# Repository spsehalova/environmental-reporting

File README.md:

# environmental-reporting

**WORK IN PROGRESS**

Enviromentalne merania

## Mesured parameters

| Parameter					| Unit			| Description							| Module									| Range			|
|---------------------------|---------------|---------------------------------------|-------------------------------------------|---------------|
| Temperature				| °C			| Ambient temperature					| BME680 									|				|
| Humidity					| %				| Relative humidity						| BME680 									|				|
| Pressure					| hPa			| Atmospheric pressure					| BME680 									|				|
| IAQ						| adaptive IAQ	| Indoor air quality index				| BME680 									| 0 - 500   	|
| sIAQ						| unscaled IAQ	| static indoor air quality index		| BME680 									| 0 - 10171		|
| eCO₂						| ppm			| Equivalent CO₂ concentration			| BME680 									| 0.5 - 1000	|
| CO₂						| ppm			| CO₂ concentration						| SEN63C 									| 				|
| bVOC						| ppm			| breath volatile organic compounds		| BME680 									| 400 - ...		|
| Compensated Gas Resistace	| Ohm			| Compensated gas resistance			| BME680 									|				|
| Gas Percentage			| %				| Gas percentage						| BME680 									|				|
| Light						| lux			| Ambient light intensity				| BH1750									|				|
| Noise						| rel dB		| Ambient noise level					| INMP441									|				|
| PM2.5/1.0/4.0/10.0		| mg/m³			| Particulate matter x concentration	| SEN63C									|				|
| Nearby Device Count		| count			| Number of nearby BLE devices			| ESP32										|				|
| Dew Point					| °C			| Dew point temperature					| Calculated from Temperature and Humidity	|				| 
| Absolute Humidity			| g/m³			| Absolute humidity						| Calculated from Temperature and Humidity	|				|
| Mold Risk 				| VTT Index		| Mold risk index						| Calculated from Temperature and Humidity	| 1 - 3			|
| Heat Index				| °C			| Heat index temperature				| Calculated from Temperature and Humidity	|				|

<!-- 
maybe https://www.soselectronic.com/sk-sk/products/sensirion/sen69c-sin-t-506264

- https://www.bosch-sensortec.com/media/boschsensortec/downloads/datasheets/bst-bme680-ds001.pdf
- https://cdn.soselectronic.com/productdata/91/1d/f677fd87/sen65-sin-t.pdf
- https://siov.sk/wp-content/uploads/2026/08/Metodika-CEOVP-aktualizacia-4-2026-i.pdf (s. 67)
- http://siov.sk/wp-content/uploads/2026/05/Strategia-kvality-1.zip - halova s. 84
- https://www.sos.sk/a_info/resource/c/sensirion/Sensirion_Humidity_at_a_Glance_V1.pdf
- https://github.com/Sensirion/arduino-i2c-sen63c
-->

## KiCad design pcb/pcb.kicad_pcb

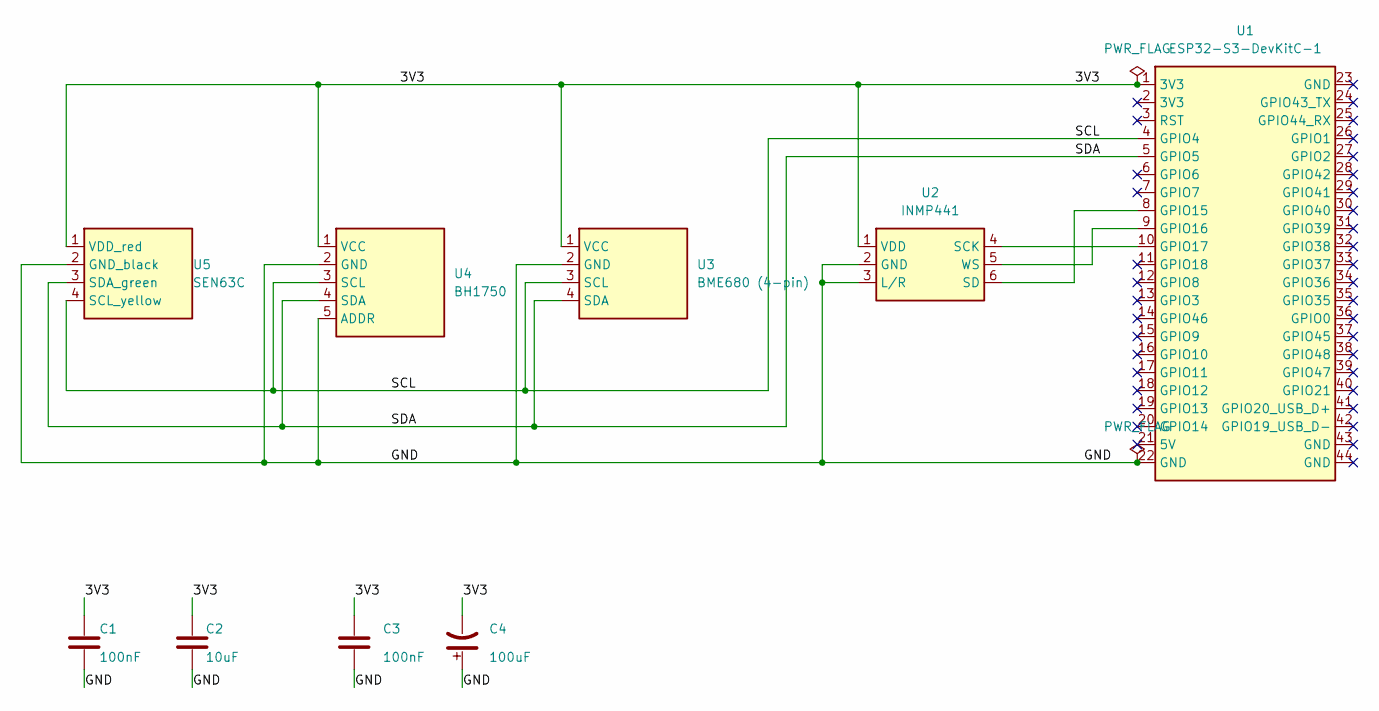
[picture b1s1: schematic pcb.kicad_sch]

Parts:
C1, C3: 100nF; C_0805_2012Metric
C2: 10uF; C_0805_2012Metric
C4: 100uF; CP_Radial_D5.0mm_P2.00mm
U1: ESP32-S3-DevKitC-1
U2: INMP441; PinSocket_1x06_P2.54mm_Vertical
U3: BME680 (4-pin); PinSocket_1x04_P2.54mm_Vertical
U4: BH1750; PinSocket_1x05_P2.54mm_Vertical
U5: SEN63C; PinSocket_1x04_P2.54mm_Vertical

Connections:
/3V3: C1.1, C2.1, C3.1, C4.1, U1.1 (3V3), U2.1 (VDD), U3.1 (VCC), U4.1 (VCC), U5.1 (VDD_red)
/GND: C1.2, C2.2, C3.2, C4.2, U1.22 (GND), U2.2 (GND), U2.3 (L/R), U3.2 (GND), U4.2 (GND), U4.5 (ADDR), U5.2 (GND_black)
/SCL: U1.4 (GPIO4), U3.3 (SCL), U4.3 (SCL), U5.4 (SCL_yellow)
/SDA: U1.5 (GPIO5), U3.4 (SDA), U4.4 (SDA), U5.3 (SDA_green)
unnamed: U1.8 (GPIO15), U2.6 (SD)
unnamed: U1.9 (GPIO16), U2.5 (WS)
unnamed: U1.10 (GPIO17), U2.4 (SCK)

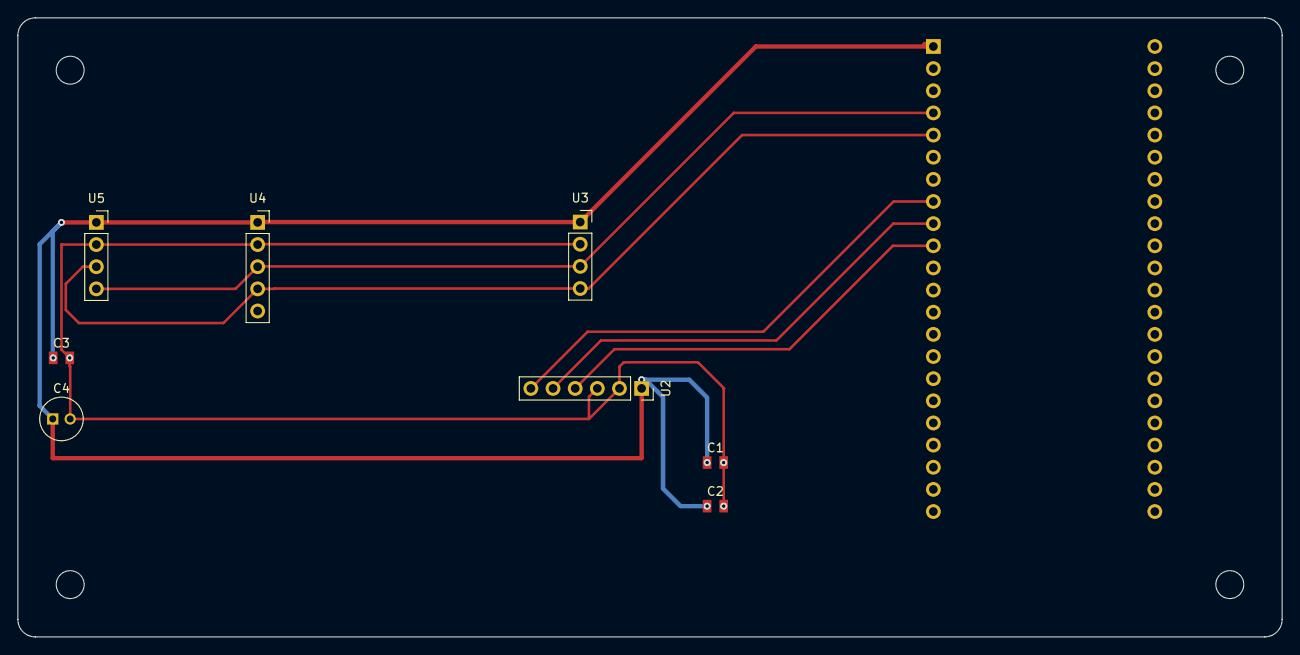
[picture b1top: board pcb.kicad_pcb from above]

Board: 2 copper layers, 145.0 x 71.0 mm, 9 parts (0 on the bottom side), 7 nets.
